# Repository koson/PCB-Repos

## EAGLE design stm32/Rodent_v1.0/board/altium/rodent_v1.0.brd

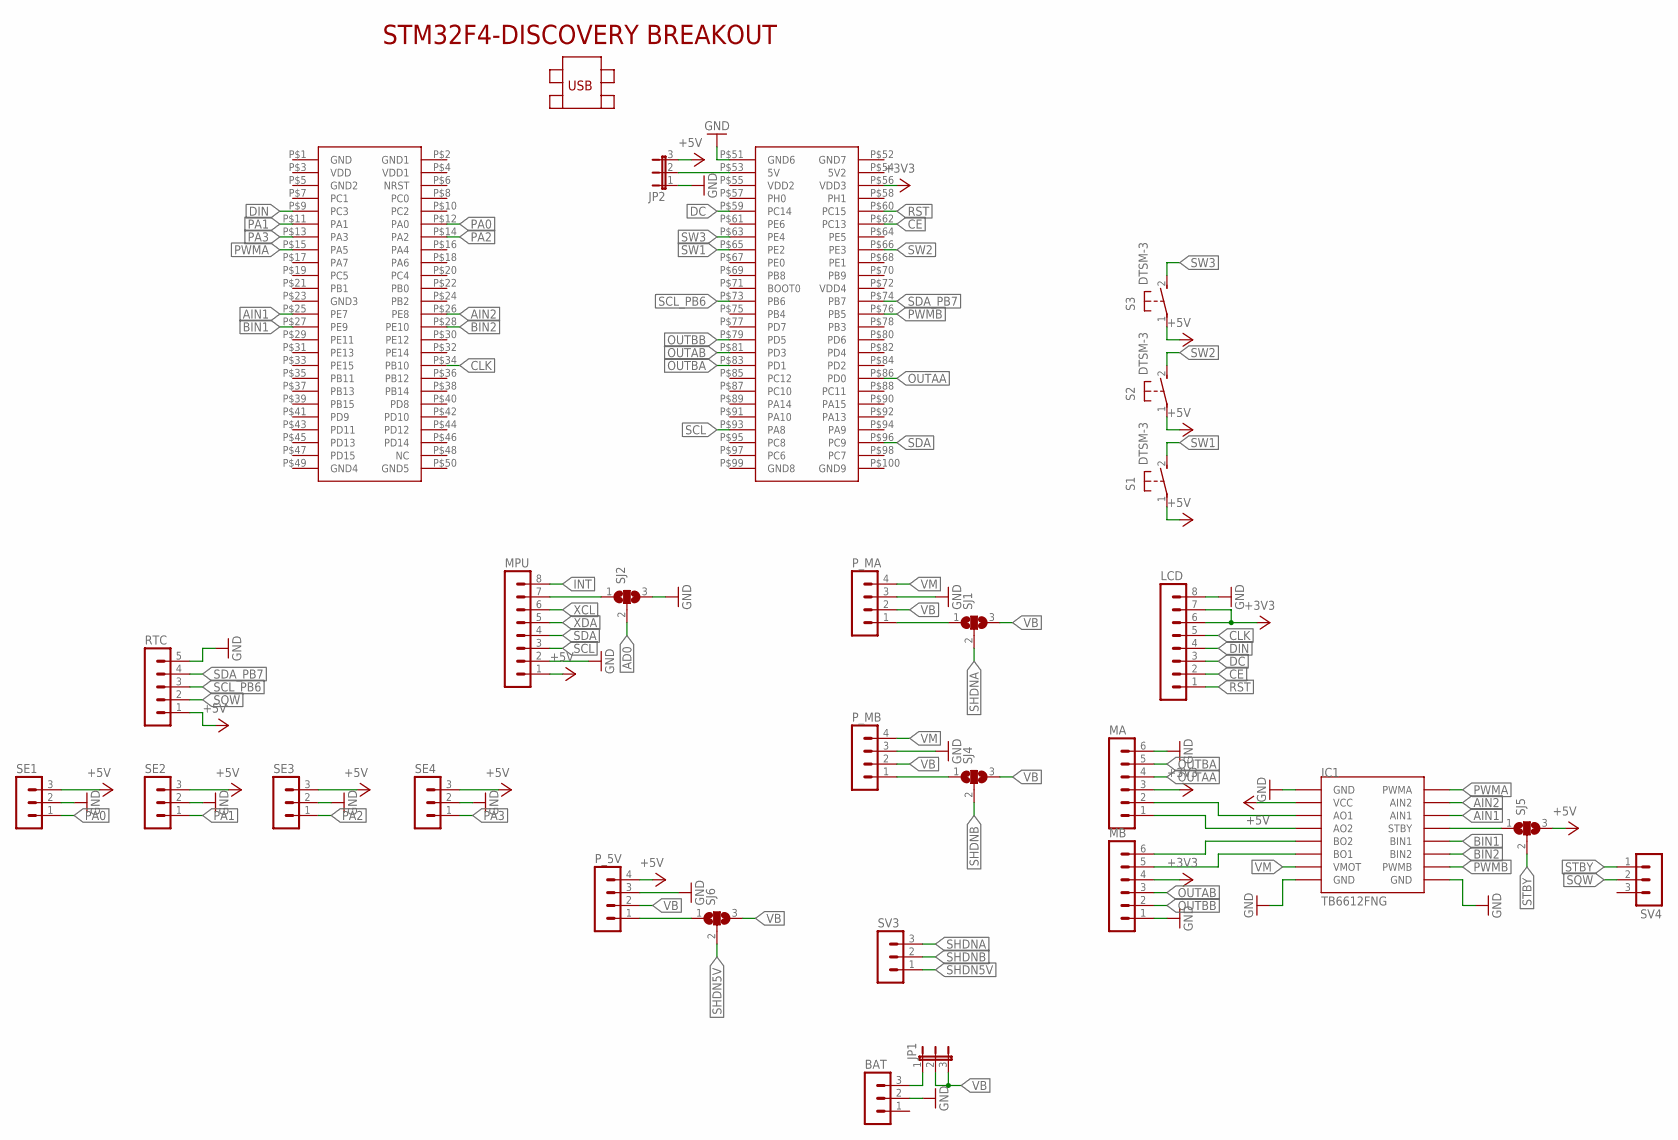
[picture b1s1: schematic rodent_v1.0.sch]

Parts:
BAT: MA03-1
IC1: MODUL_POLOLU
JP1, JP2: JP2E; JP2
LCD: MA08-1
MA: MA06-1
MB: MA06-1
MPU: MA08-1
P_5V: MA04-1
P_MA: MA04-1
P_MB: MA04-1
RTC: MA05-1
S1, S2, S3: DTSM-3
SE1, SE2, SE3, SE4: MA03-1
SJ1, SJ2, SJ4, SJ5, SJ6: SJ2WW; SJ_2W
SV3, SV4: MA03-1
U$1: STM32F4-DISCOVERY

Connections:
+3V3: LCD.6, LCD.7, MA.3, MB.4, U$1.P$56 (VDD3)
+5V: IC1.VCC, JP2.3, MPU.1, P_5V.4, RTC.1, S1.1, S2.1, S3.1, SE1.3, SE2.3, SE3.3, SE4.3, SJ5.3
AD0: SJ2.2
AIN1: IC1.AIN1, U$1.P$25 (PE7)
AIN2: IC1.AIN2, U$1.P$26 (PE8)
BIN1: IC1.BIN1, U$1.P$27 (PE9)
BIN2: IC1.BIN2, U$1.P$28 (PE10)
CE: LCD.2, U$1.P$62 (PC13)
CLK: LCD.5, U$1.P$34 (PB10)
DC: LCD.3, U$1.P$59 (PC14)
DIN: LCD.4, U$1.P$9 (PC3)
GND: BAT.2, IC1.GND1 (GND), IC1.GND2 (GND), IC1.GND3 (GND), JP2.1, LCD.8, MA.6, MB.1, MPU.2, P_5V.3, P_MA.3, P_MB.3, RTC.5, SE1.2, SE2.2, SE3.2, SE4.2, SJ2.3, U$1.P$51 (GND6)
INT: MPU.8
unnamed: P_MA.1, SJ1.1
unnamed: BAT.3, JP1.1
unnamed: P_MB.1, SJ4.1
unnamed: MPU.7, SJ2.1
unnamed: JP2.2, U$1.P$53 (5V)
unnamed: IC1.STBY, SJ5.1
unnamed: IC1.AO1, MA.2
unnamed: IC1.A02 (AO2), MA.1
unnamed: IC1.BO2, MB.6
unnamed: IC1.BO1, MB.5
unnamed: P_5V.1, SJ6.1
OUTAA: MA.4, U$1.P$86 (PD0)
OUTAB: MB.3, U$1.P$81 (PD3)
OUTBA: MA.5, U$1.P$83 (PD1)
OUTBB: MB.2, U$1.P$79 (PD5)
PA0: SE1.1, U$1.P$12 (PA0)
PA1: SE2.1, U$1.P$11 (PA1)
PA2: SE3.1, U$1.P$14 (PA2)
PA3: SE4.1, U$1.P$13 (PA3)
PWMA: IC1.PWMA, U$1.P$15 (PA5)
PWMB: IC1.PWMB, U$1.P$76 (PB5)
RST: LCD.1, U$1.P$60 (PC15)
SCL: MPU.3, U$1.P$93 (PA8)
SCL_PB6: RTC.3, U$1.P$73 (PB6)
SDA: MPU.4, U$1.P$96 (PC9)
SDA_PB7: RTC.4, U$1.P$74 (PB7)
SHDN5V: SJ6.2, SV3.1
SHDNA: SJ1.2, SV3.3
SHDNB: SJ4.2, SV3.2
SQW: RTC.2, SV4.2
STBY: SJ5.2, SV4.1
SW1: S1.2, U$1.P$65 (PE2)
SW2: S2.2, U$1.P$66 (PE3)
SW3: S3.2, U$1.P$63 (PE4)
VB: JP1.2, JP1.3, P_5V.2, P_MA.2, P_MB.2, SJ1.3, SJ4.3, SJ6.3
VM: IC1.VMOT, P_MA.4, P_MB.4
XCL: MPU.6
XDA: MPU.5

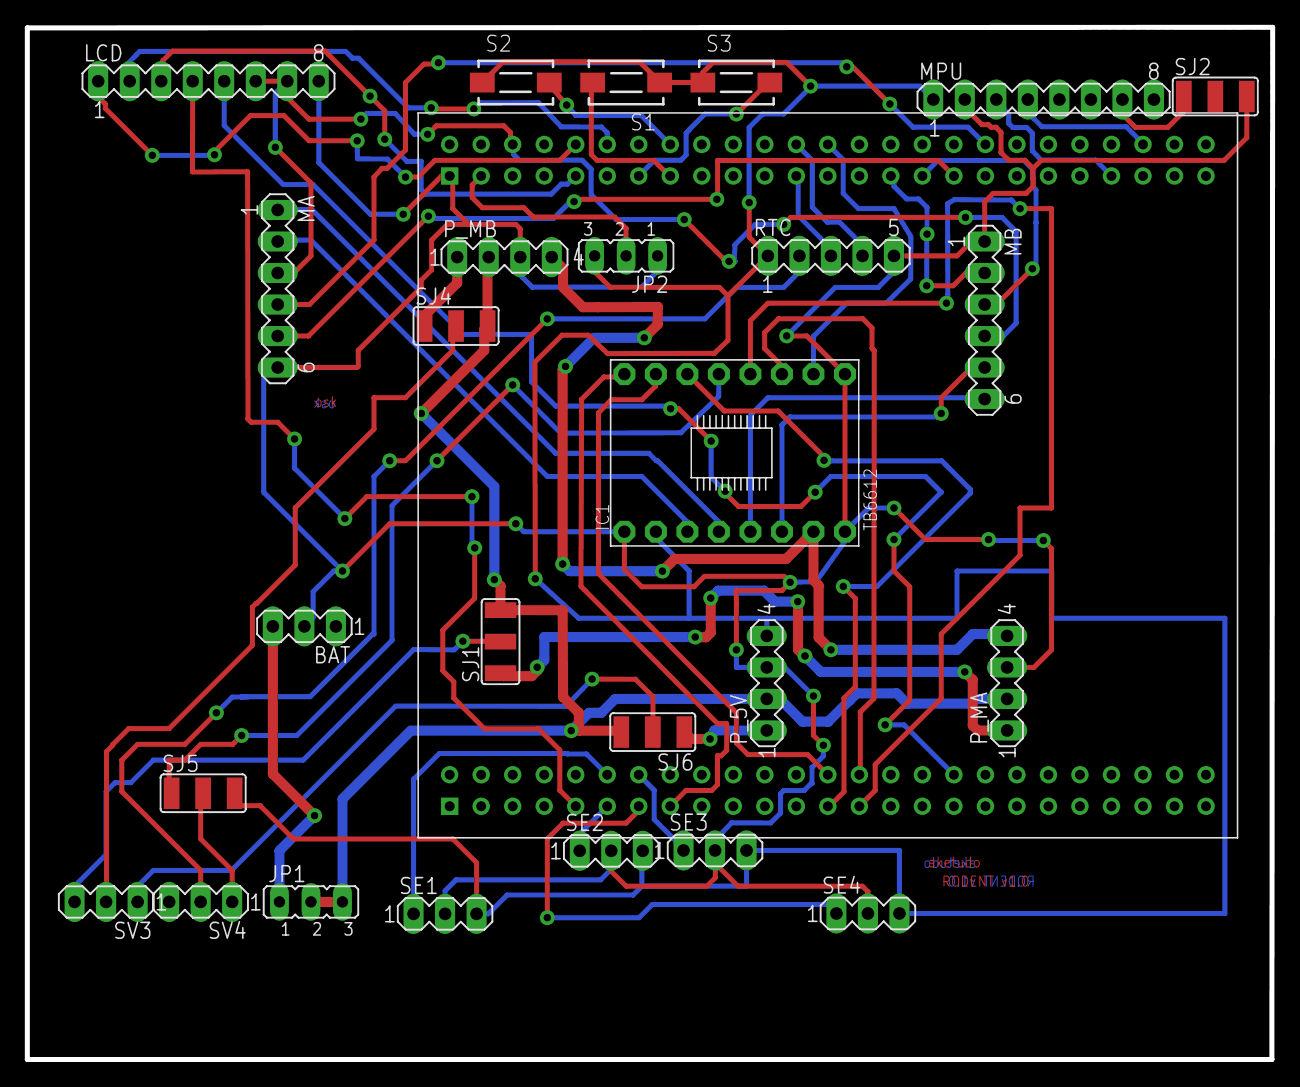
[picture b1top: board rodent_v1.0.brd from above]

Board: 2 copper layers, 100.4 x 83.2 mm, 27 parts (0 on the bottom side), 47 nets.

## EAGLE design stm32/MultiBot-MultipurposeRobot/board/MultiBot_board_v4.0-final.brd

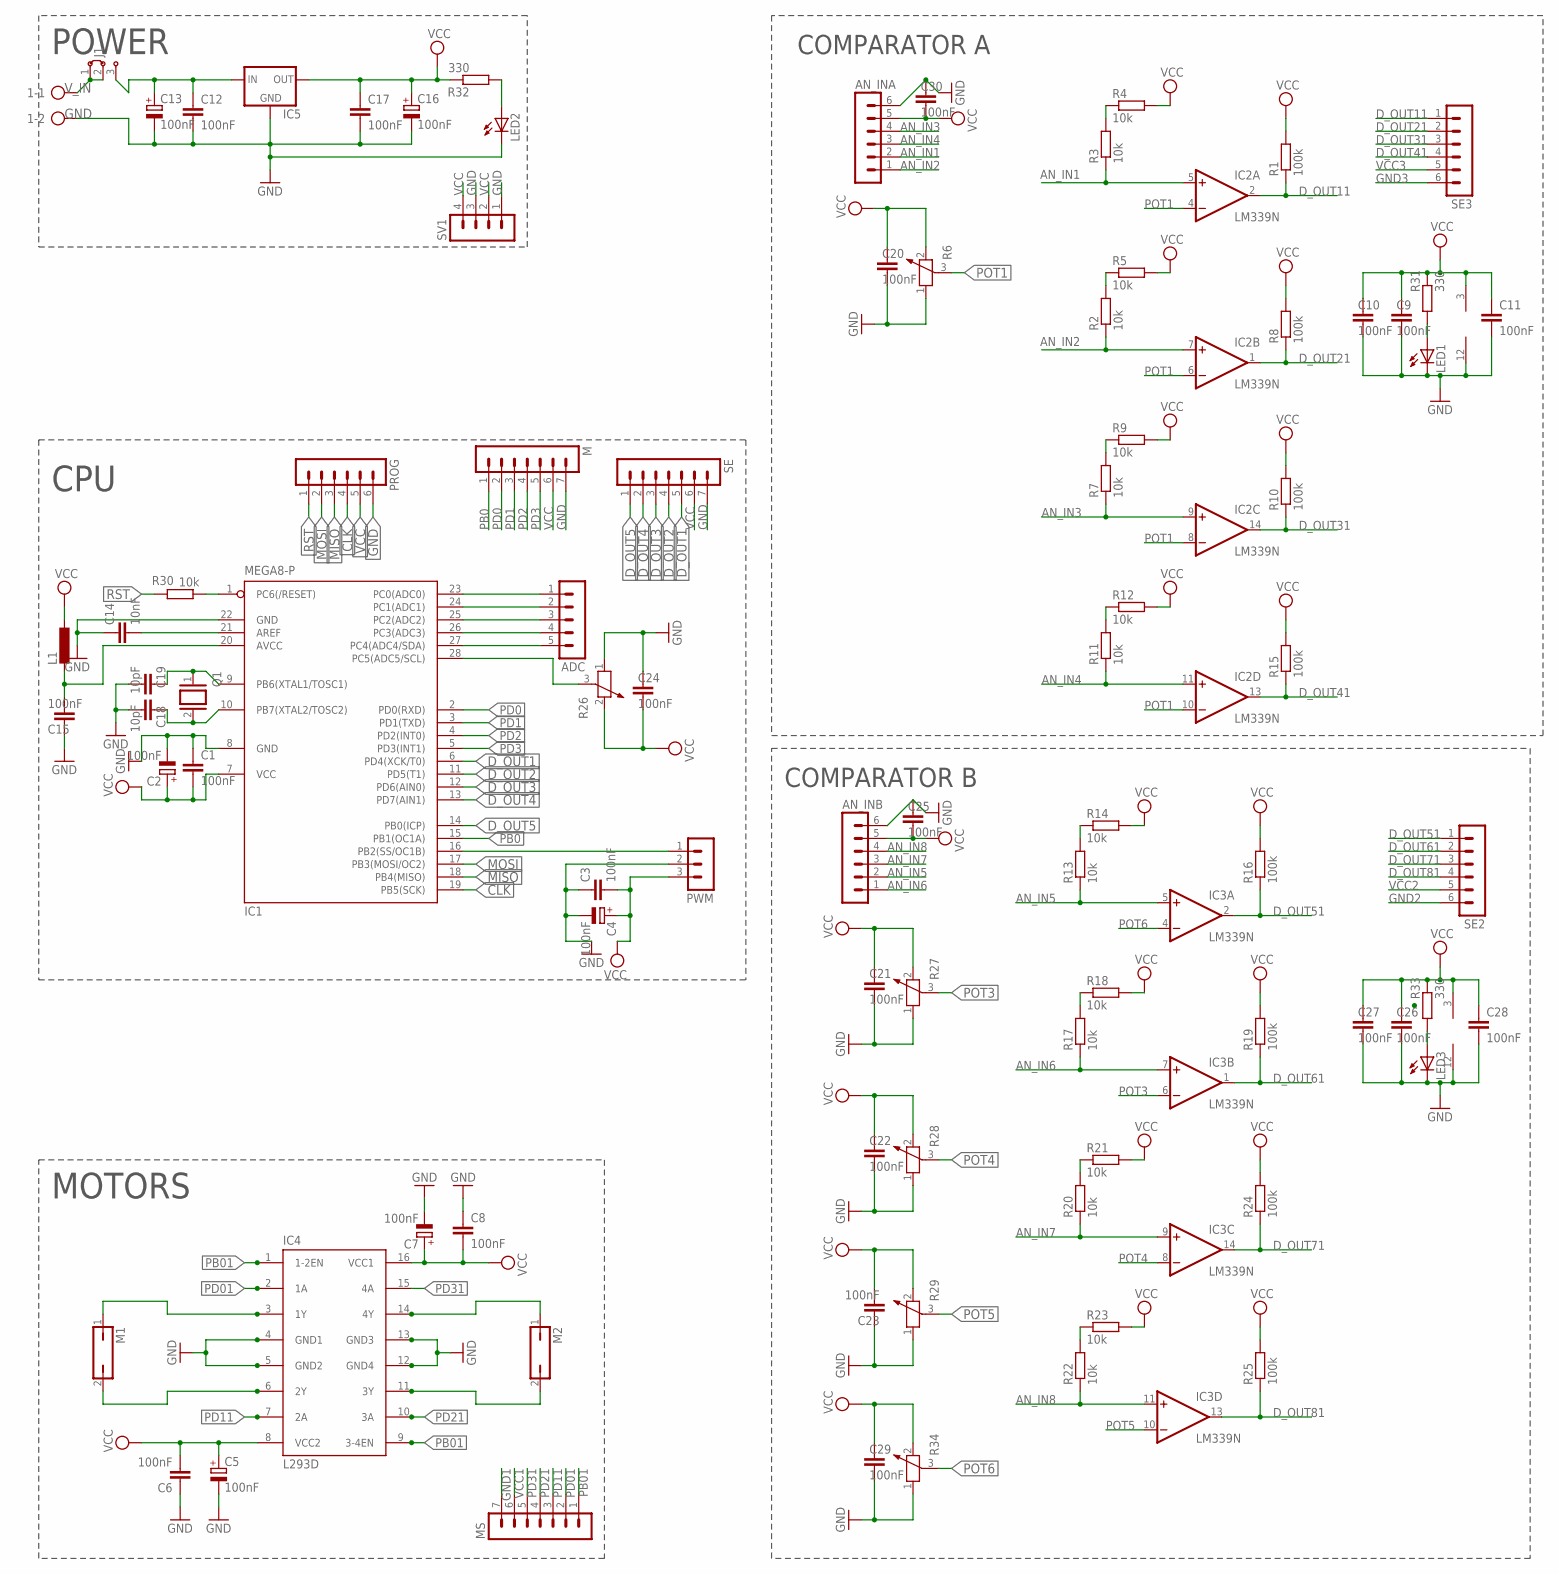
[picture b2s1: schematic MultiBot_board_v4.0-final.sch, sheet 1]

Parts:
1: AK300/2
ADC: MA05-1
AN_INA: MA06-1
AN_INB: MA06-1
C1, C3, C6, C8, C9, C10, C11, C12, C15, C17, C20, C21, C22, C23, C24, C25, C26, C27, C28, C29, C30: 100nF; C025-024X044
C2, C4, C5, C7, C13, C16: 100nF; SANYO-OSCON_A
C14: 10nF; C025-024X044
C18, C19: 10pF; C025-024X044
IC1: MEGA8-P; DIL28-3
IC2, IC3: LM339N; DIL14
IC4: L293D; DIL16
IC5: 78XXS
J1: J2X2MM; 04C
L1: L-EU0204/5; 0204/5
LED1, LED2, LED3: LED_ELD260; LED_LD260
M: MA07-1
M1, M2: JP1Q; JP1
MS: MA07-1
PROG: MA06-1
PWM: MA03-1
Q1: XTAL/S; QS
R1, R8, R10, R15, R16, R19, R24, R25: 100k; 0204/5
R2, R3, R4, R5, R7, R9, R11, R12, R13, R14, R17, R18, R20, R21, R22, R23, R30: 10k; 0204/5
R6, R26, R27, R28, R29, R34: POTENTIOMETER_PT-10; PT-10
R31, R32, R33: 330; 0204/5
SE: MA07-1
SE2, SE3: MA06-1
SV1: MA04-1

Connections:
AN_IN1: AN_INA.2, IC2.5 (+IN), R3.1
AN_IN2: AN_INA.1, IC2.7 (+IN), R2.1
AN_IN3: AN_INA.4, IC2.9 (+IN), R7.1
AN_IN4: AN_INA.3, IC2.11 (+IN), R11.1
AN_IN5: AN_INB.2, IC3.5 (+IN), R13.1
AN_IN6: AN_INB.1, IC3.7 (+IN), R17.1
AN_IN7: AN_INB.3, IC3.9 (+IN), R20.1
AN_IN8: AN_INB.4, IC3.11 (+IN), R22.1
CLK: IC1.19 (PB5(SCK)), PROG.4
D_OUT1: IC1.6 (PD4(XCK/T0)), SE.5
D_OUT2: IC1.11 (PD5(T1)), SE.4
D_OUT3: IC1.12 (PD6(AIN0)), SE.3
D_OUT4: IC1.13 (PD7(AIN1)), SE.2
D_OUT5: IC1.14 (PB0(ICP)), SE.1
D_OUT11: IC2.2 (OUT), R1.1, SE3.1
D_OUT21: IC2.1 (OUT), R8.1, SE3.2
D_OUT31: IC2.14 (OUT), R10.1, SE3.3
D_OUT41: IC2.13 (OUT), R15.1, SE3.4
D_OUT51: IC3.2 (OUT), R16.1, SE2.1
D_OUT61: IC3.1 (OUT), R19.1, SE2.2
D_OUT71: IC3.14 (OUT), R24.1, SE2.3
D_OUT81: IC3.13 (OUT), R25.1, SE2.4
GND: 1.2, C1.1, C2.-, C3.1, C4.-, C12.2, C13.-, C14.1, C15.1, C16.-, C17.2, C18.2, C19.2, C24.1, IC1.8 (GND), IC1.22 (GND), IC5.GND, LED2.K (C), M.7, PROG.6, PWM.2, R26.1, SE.7, SV1.1, SV1.3
GND1: C5.-, C6.1, C7.-, C8.1, IC4.4 (GND1), IC4.5 (GND2), IC4.12 (GND4), IC4.13 (GND3), MS.7
GND2: AN_INB.6, C21.2, C22.2, C23.1, C25.1, C26.2, C27.2, C28.2, C29.2, IC3.12 (GND), LED3.K (C), R27.1, R28.1, R29.1, R34.1, SE2.6
GND3: AN_INA.6, C9.2, C10.2, C11.2, C20.2, C30.1, IC2.12 (GND), LED1.K (C), R6.1, SE3.6
MISO: IC1.18 (PB4(MISO)), PROG.3
MOSI: IC1.17 (PB3(MOSI/OC2)), PROG.2
unnamed: IC4.3 (1Y), M1.1
unnamed: IC4.6 (2Y), M1.2
unnamed: IC4.14 (4Y), M2.1
unnamed: IC4.11 (3Y), M2.2
unnamed: R7.2, R9.1
unnamed: LED1.A, R31.1
unnamed: R3.2, R4.1
unnamed: R2.2, R5.1
unnamed: R11.2, R12.1
unnamed: R13.2, R14.1
unnamed: R17.2, R18.1
unnamed: R20.2, R21.1
unnamed: R22.2, R23.1
unnamed: C14.2, IC1.21 (AREF)
unnamed: LED2.A, R32.1
unnamed: IC1.28 (PC5(ADC5/SCL)), R26.3
unnamed: ADC.1, IC1.23 (PC0(ADC0))
unnamed: ADC.2, IC1.24 (PC1(ADC1))
unnamed: ADC.3, IC1.25 (PC2(ADC2))
unnamed: ADC.4, IC1.26 (PC3(ADC3))
unnamed: ADC.5, IC1.27 (PC4(ADC4/SDA))
unnamed: IC1.1 (PC6(/RESET)), R30.1
unnamed: C18.1, IC1.10 (PB7(XTAL2/TOSC2)), Q1.2
unnamed: C19.1, IC1.9 (PB6(XTAL1/TOSC1)), Q1.1
unnamed: C15.2, IC1.20 (AVCC), L1.2
unnamed: 1.1, J1.1, J1.2
unnamed: LED3.A, R33.1
PB0: IC1.15 (PB1(OC1A)), M.1
PB01: IC4.1 (1-2EN), IC4.9 (3-4EN), MS.1
PD0: IC1.2 (PD0(RXD)), M.2
PD1: IC1.3 (PD1(TXD)), M.3
PD01: IC4.2 (1A), MS.2
PD2: IC1.4 (PD2(INT0)), M.4
PD3: IC1.5 (PD3(INT1)), M.5
PD11: IC4.7 (2A), MS.3
PD21: IC4.10 (3A), MS.4
PD31: IC4.15 (4A), MS.5
POT1: IC2.4 (-IN), IC2.6 (-IN), IC2.8 (-IN), IC2.10 (-IN), R6.3
POT3: IC3.6 (-IN), R27.3
POT4: IC3.8 (-IN), R28.3
POT5: IC3.10 (-IN), R29.3
POT6: IC3.4 (-IN), R34.3
PWM2: IC1.16 (PB2(SS/OC1B)), PWM.1
RST: PROG.1, R30.2
VCC: C1.2, C2.+, C3.2, C4.+, C16.+, C17.1, C24.2, IC1.7 (VCC), IC5.OUT, L1.1, M.6, PROG.5, PWM.3, R26.2, R32.2, SE.6, SV1.2, SV1.4
VCC1: C5.+, C6.2, C7.+, C8.2, IC4.8 (VCC2), IC4.16 (VCC1), MS.6
VCC2: AN_INB.5, C21.1, C22.1, C23.2, C25.2, C26.1, C27.1, C28.1, C29.1, IC3.3 (V+), R14.2, R16.2, R18.2, R19.2, R21.2, R23.2, R24.2, R25.2, R27.2, R28.2, R29.2, R33.2, R34.2, SE2.5
VCC3: AN_INA.5, C9.1, C10.1, C11.1, C20.1, C30.2, IC2.3 (V+), R1.2, R4.2, R5.2, R6.2, R8.2, R9.2, R10.2, R12.2, R15.2, R31.2, SE3.5
V_IN: C12.1, C13.+, IC5.IN, J1.3

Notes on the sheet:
MOTORS
CPU
POWER
COMPARATOR A
COMPARATOR B

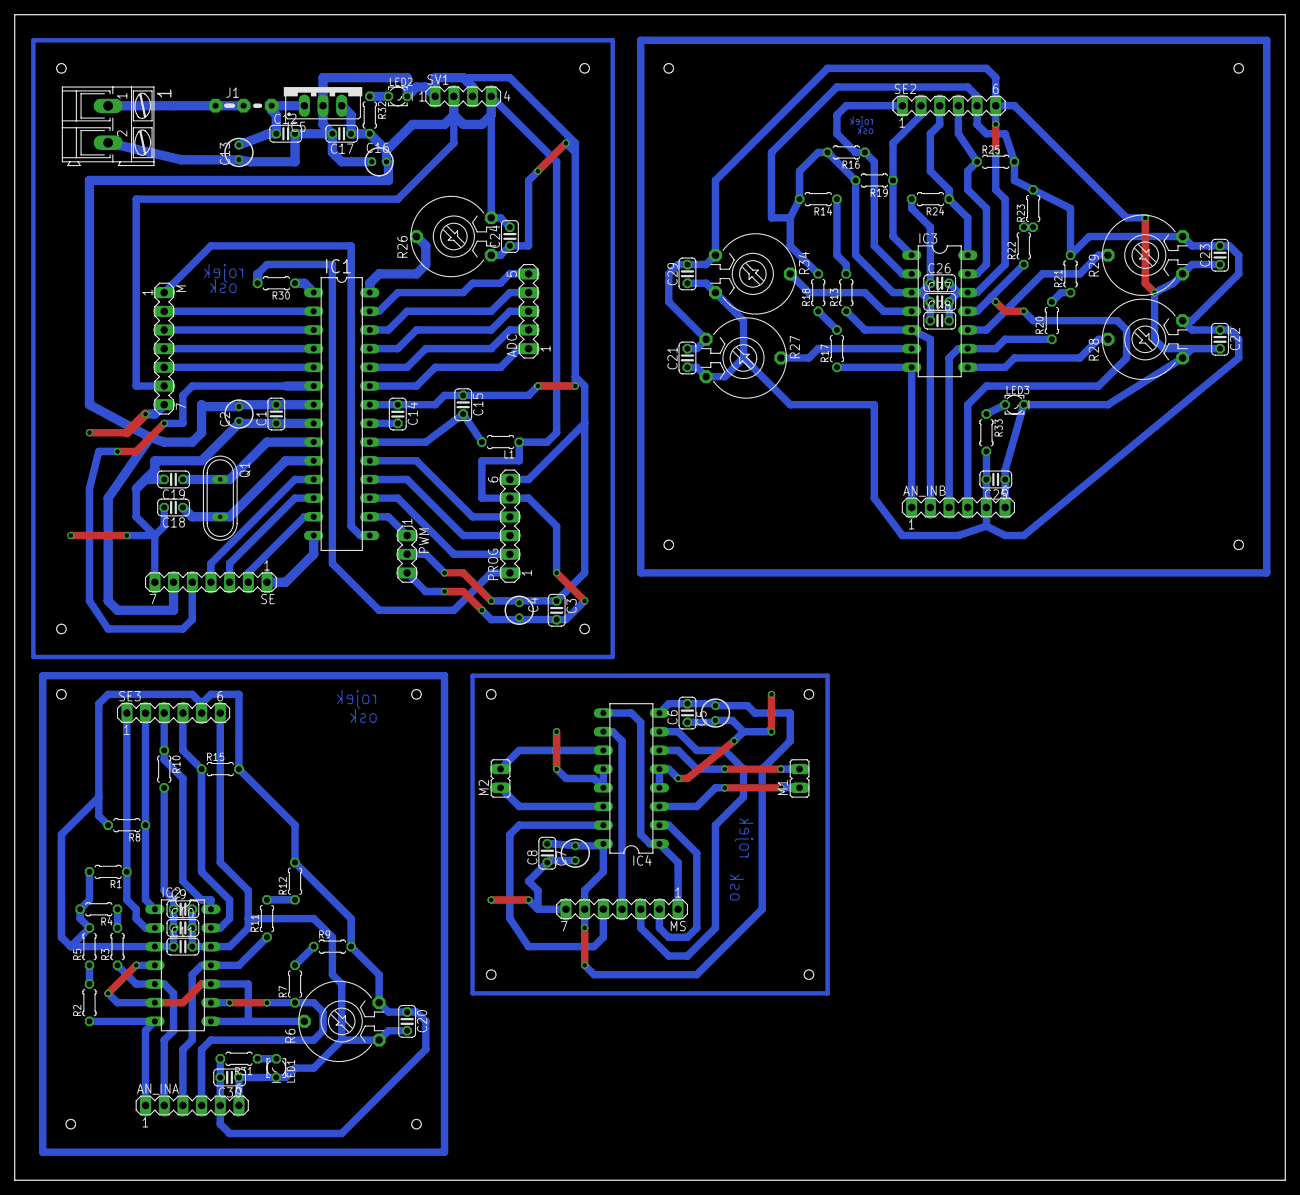
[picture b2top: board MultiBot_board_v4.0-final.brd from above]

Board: 2 copper layers, 172.7 x 158.4 mm, 89 parts (0 on the bottom side), 77 nets.

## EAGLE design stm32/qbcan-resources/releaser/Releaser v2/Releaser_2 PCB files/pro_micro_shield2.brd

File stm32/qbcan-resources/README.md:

# QBCAN Resources

A collection of CAD files, drivers and other resources related to some projects from Open Cosmos

Please see the wiki for more details at http://doc.open-cosmos.com/Special:AllPages

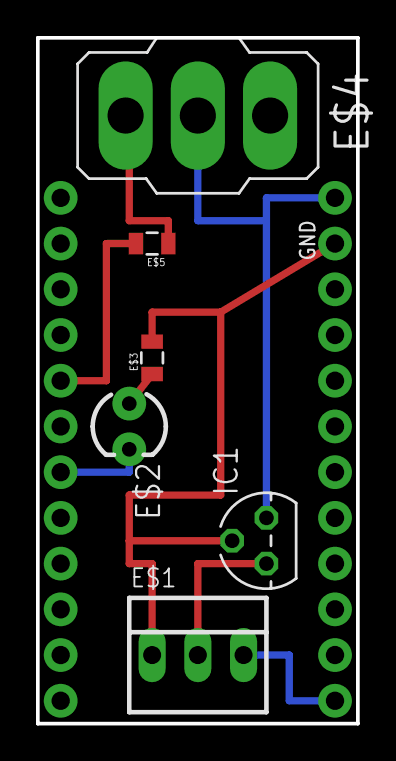
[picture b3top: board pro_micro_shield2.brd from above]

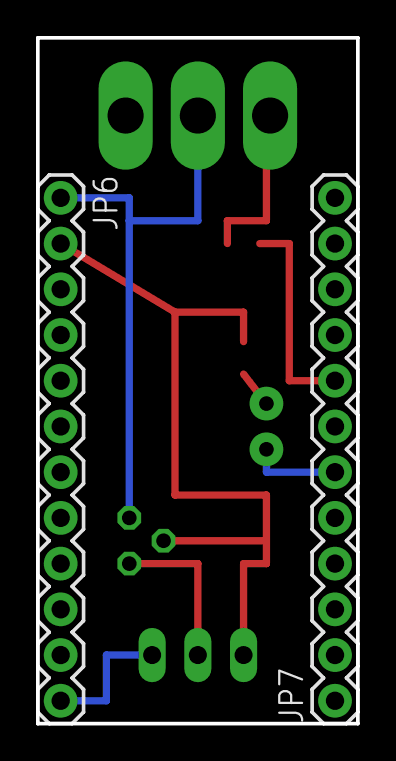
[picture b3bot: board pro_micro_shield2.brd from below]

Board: 2 copper layers, 17.8 x 38.1 mm, 8 parts (2 on the bottom side), 8 nets.

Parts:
E$1: 22-23-2031
E$2: LED3MM
E$3, E$5: 0805
E$4: 320-916
IC1: 78L05Z; TO92
JP6, JP7: 1X12

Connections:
GND: E$1.1, E$3.2, IC1.2, JP6.2
S$1: E$4.2, IC1.3, JP6.1
S$2: E$5.2, JP7.8
S$3: E$1.3, JP6.12
S$4: E$1.2, IC1.1
S$5: E$4.3, E$5.1
S$6: E$2.A, E$3.1
S$7: E$2.K, JP7.6

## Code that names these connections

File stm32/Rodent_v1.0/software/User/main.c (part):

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/*--------------------MOTORS_OPERATING---------------------------------
power_percent - percent of pwm duty cycle
MOTOR_A - Right 
				 Stering Port A: PE7, PE8
				 PWM_A Port: PA5
MOTOR_B - Left 
				 Stering Port B: PE9, PE10
				 PWM_B Port: PB5*/

void MotorSystemInit()
{
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	/* 1 kHz = 1ms = 1000us */
	TM_PWM_InitTimer(TIM4, &TIM4_Data, 40000);
	
	/* Initialize PWM on TIM2, Channel 1 and PinsPack 2 = PB5 */
	TM_PWM_InitChannel(&TIM4_Data, TM_PWM_Channel_3, TM_PWM_PinsPack_1);
	
	//TM_PWM_InitTimer(TIM4, &TIM4_Data, 40000);
	/* Initialize PWM on TIM4, Channel 2 and PinsPack 2 = PB5 */
	TM_PWM_InitChannel(&TIM4_Data, TM_PWM_Channel_4, TM_PWM_PinsPack_1);
	
//	/* Initialize PWM on TIM4, Channel 2 and PinsPack 2 = PB3 */
//	TM_PWM_InitChannel(&TIM2_Data, TM_PWM_Channel_2, TM_PWM_PinsPack_2);
	
		/* Initialize Motors GPIO*/
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	/* Initialize motors system*/
	MotorSystemInit();	
	
	/* Initialize USART6, 115200 baud, TX: PC6 RX: PC7*/
	TM_USART_Init(USART6, TM_USART_PinsPack_1, 115200);
	
/* Initialize RTC DS1307 */
		/* RTC SQW External interrupt PE0*/
	if (TM_EXTI_Attach(GPIOE, GPIO_Pin_0, TM_EXTI_Trigger_Falling) != TM_EXTI_Result_Ok) {
			TM_USART_Puts(USART6, "RTC EXIT Error\n");
	while(1);
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	PCD8544_Init(0x40);
	
/* Initialize ADC */
	TM_ADC_Init(ADC1, ADC_Channel_11); //ADC Port PC1
	TM_ADC_Init(ADC1, ADC_Channel_1);	//ADC Port PA1
	TM_ADC_Init(ADC1, ADC_Channel_2);	//ADC Port PA2
	TM_ADC_Init(ADC1, ADC_Channel_3);	//ADC Port PA3	
	
/* Initialize buttons GPIO*/
	TM_GPIO_Init(GPIOE, GPIO_Pin_2 | GPIO_Pin_3 | GPIO_Pin_4, TM_GPIO_Mode_IN, TM_GPIO_OType_PP, TM_GPIO_PuPd_DOWN, TM_GPIO_Speed_High);
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
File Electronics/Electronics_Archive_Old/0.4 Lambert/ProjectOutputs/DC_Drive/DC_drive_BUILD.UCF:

NET "LEDS0" LOC=P185;
NET "LEDS1" LOC=P184;
NET "LEDS2" LOC=P183;
NET "PB0" LOC=P127;
NET "PB1" LOC=P126;
NET "PB2" LOC=P125;
NET "PB3" LOC=P123;

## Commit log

2019-10-09 add submodule
2019-10-10 add R3_Robot
2019-10-12 add submodel
2019-10-13 add sub module

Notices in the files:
parts and their libraries:
SparkFun-LED: Licensing: Creative Commons ShareAlike 4.0 International - https://creativecommons.org/licenses/by-sa/4.0
